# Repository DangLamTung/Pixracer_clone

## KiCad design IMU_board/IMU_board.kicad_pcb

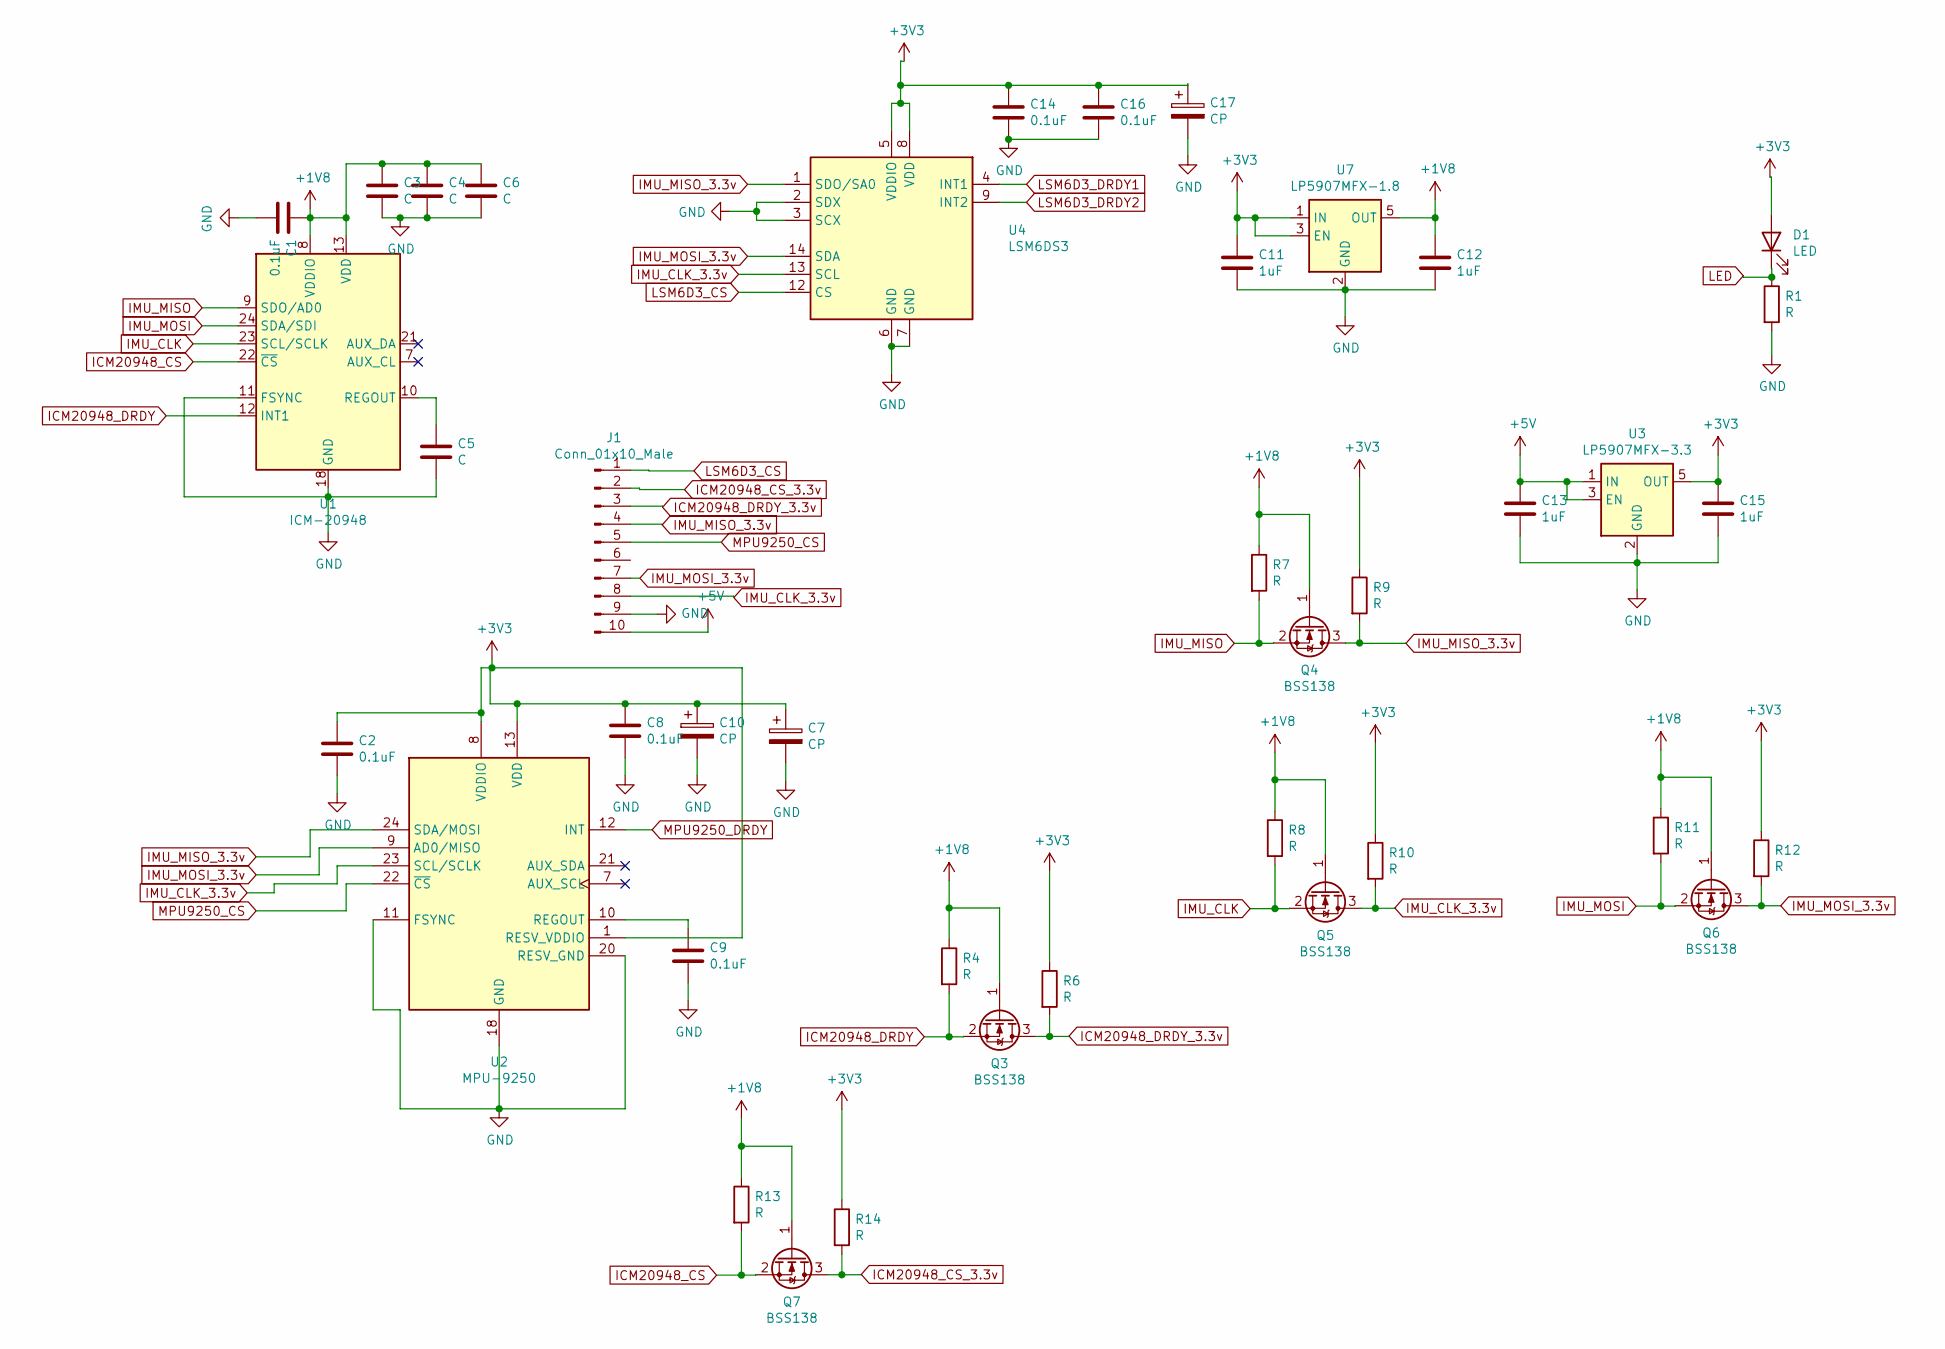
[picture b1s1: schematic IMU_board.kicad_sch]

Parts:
C1, C2, C8, C9, C14, C16: 0.1uF; C_0603_1608Metric
C3, C4, C6: C; C_0603_1608Metric_Pad1.05x0.95mm_HandSolder
C5: C; C_0603_1608Metric
C7, C17: CP; C_1206_3216Metric
C10: CP; C_0603_1608Metric_Pad1.05x0.95mm_HandSolder
C11, C12, C13, C15: 1uF; C_0603_1608Metric_Pad1.05x0.95mm_HandSolder
D1: LED; LED_0603_1608Metric_Pad1.05x0.95mm_HandSolder
J1: Conn_01x10_Male; PinHeader_1x10_P2.54mm_Vertical
Q3, Q4, Q5, Q6, Q7: BSS138; SOT-23
R1, R4, R6, R7, R8, R9, R10, R11, R12, R13, R14: R; R_0603_1608Metric_Pad1.05x0.95mm_HandSolder
U1: ICM-20948; InvenSense_QFN-24_3x3mm_P0.4mm
U2: MPU-9250; InvenSense_QFN-24_3x3mm_P0.4mm
U3: LP5907MFX-3.3; SOT-23-5
U4: LSM6DS3; LGA-14_3x2.5mm_P0.5mm_LayoutBorder3x4y
U7: LP5907MFX-1.8; SOT-23-5

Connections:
+1V8: C1.1, C3.1, C4.1, C6.1, C12.1, Q3.1 (G), Q4.1 (G), Q5.1 (G), Q6.1 (G), Q7.1 (G), R4.1, R7.1, R8.1, R11.1, R13.1, U1.8 (VDDIO), U1.13 (VDD), U7.5 (OUT)
+3V3: C2.1, C7.1, C8.1, C10.1, C11.1, C14.1, C15.1, C16.1, C17.1, D1.2 (A), R6.1, R9.1, R10.1, R12.1, R14.1, U2.1 (RESV_VDDIO), U2.8 (VDDIO), U2.13 (VDD), U3.5 (OUT), U4.5 (VDDIO), U4.8 (VDD), U7.1 (IN), U7.3 (EN)
+5V: C13.1, J1.10, U3.1 (IN), U3.3 (EN)
GND: C1.2, C2.2, C3.2, C4.2, C5.2, C6.2, C7.2, C8.2, C9.2, C10.2, C11.2, C12.2, C13.2, C14.2, C15.2, C16.2, C17.2, J1.9, R1.2, U1.11 (FSYNC), U1.18 (GND), U1.20 (GND), U2.11 (FSYNC), U2.18 (GND), U2.20 (RESV_GND), U3.2 (GND), U4.2 (SDX), U4.3 (SCX), U4.6 (GND), U4.7 (GND), U7.2 (GND)
ICM20948_CS: Q7.2 (S), R13.2, U1.22 (~CS)
ICM20948_CS_3.3v: J1.2, Q7.3 (D), R14.2
ICM20948_DRDY: Q3.2 (S), R4.2, U1.12 (INT1)
ICM20948_DRDY_3.3v: J1.3, Q3.3 (D), R6.2
IMU_CLK: Q5.2 (S), R8.2, U1.23 (SCL/SCLK)
IMU_CLK_3.3v: J1.8, Q5.3 (D), R10.2, U2.23 (SCL/SCLK), U4.13 (SCL)
IMU_MISO: Q4.2 (S), R7.2, U1.9 (SDO/AD0)
IMU_MISO_3.3v: J1.4, Q4.3 (D), R9.2, U2.24 (SDA/MOSI), U4.1 (SDO/SA0)
IMU_MOSI: Q6.2 (S), R11.2, U1.24 (SDA/SDI)
IMU_MOSI_3.3v: J1.7, Q6.3 (D), R12.2, U2.9 (AD0/MISO), U4.14 (SDA)
LED: D1.1 (K), R1.1
LSM6D3_CS: J1.1, U4.12 (CS)
LSM6D3_DRDY1: U4.4 (INT1)
LSM6D3_DRDY2: U4.9 (INT2)
MPU9250_CS: J1.5, U2.22 (~CS)
MPU9250_DRDY: U2.12 (INT)
unnamed: C5.1, U1.10 (REGOUT)
unnamed: C9.1, U2.10 (REGOUT)

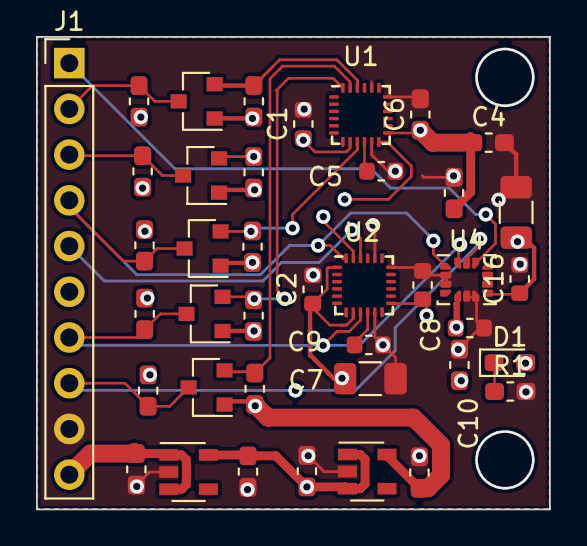
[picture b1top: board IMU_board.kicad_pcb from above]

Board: 4 copper layers, 28.5 x 26.2 mm, 40 parts (0 on the bottom side), 19 nets.

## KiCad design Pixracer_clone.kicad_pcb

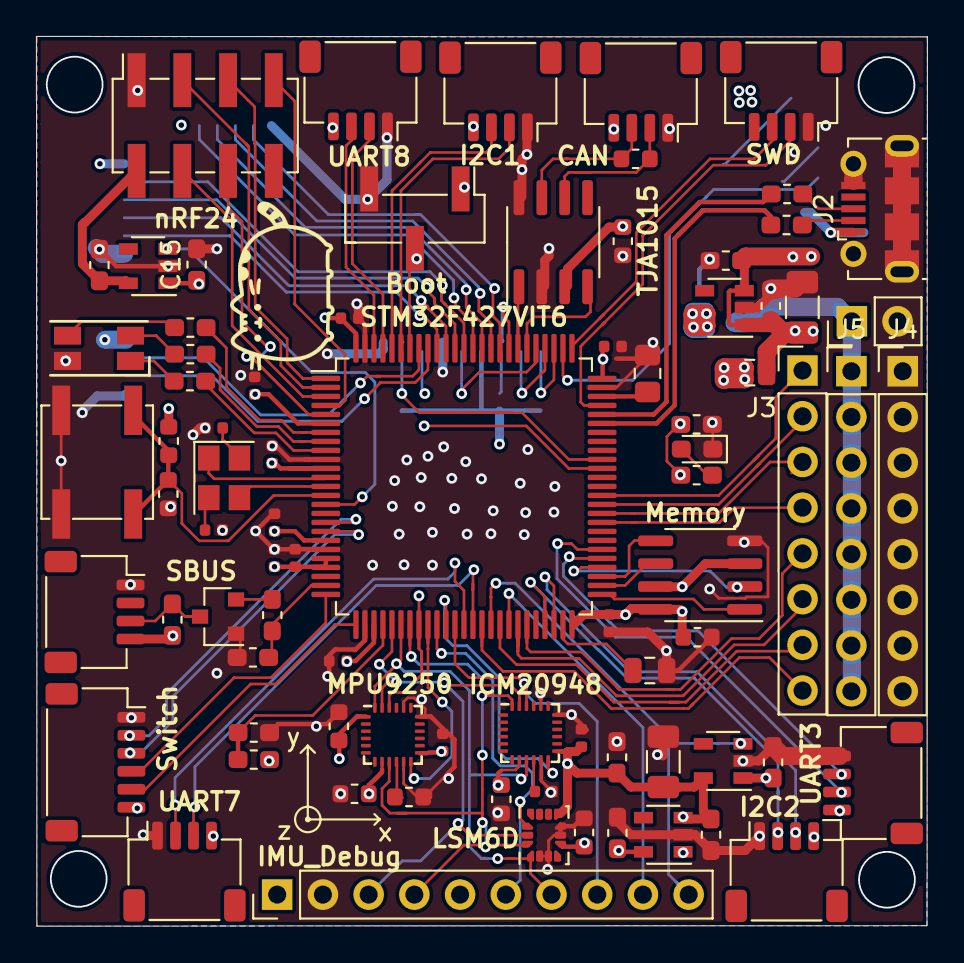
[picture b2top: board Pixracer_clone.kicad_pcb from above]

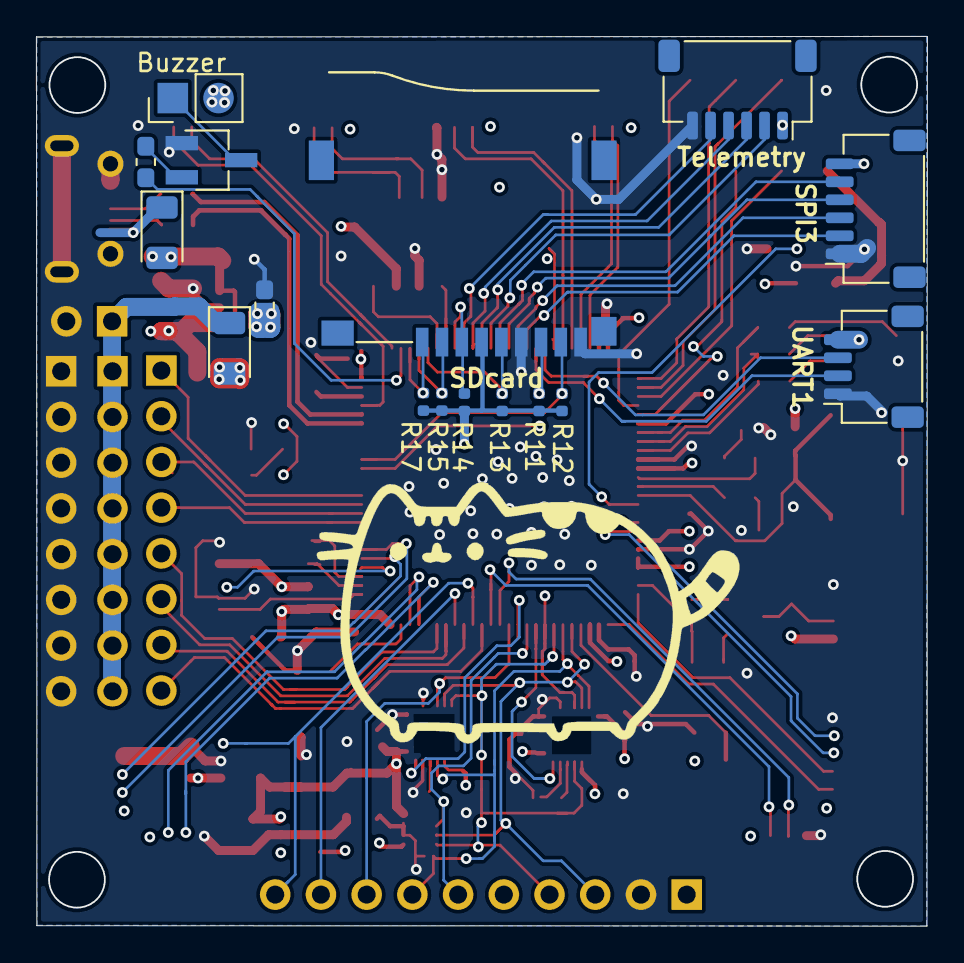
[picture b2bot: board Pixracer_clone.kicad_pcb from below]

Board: 4 copper layers, 49.5 x 49.4 mm, 98 parts (16 on the bottom side), 101 nets.

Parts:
Boot: Conn_01x03_Male; PinHeader_1x03_P2.54mm_Vertical_SMD_Pin1Left
Buzzer: Conn_01x02_Male; PinHeader_1x02_P2.54mm_Vertical
C1: CP; C_0805_2012Metric_Pad1.15x1.40mm_HandSolder
C2, C4: 22p; C_0402_1005Metric
C3: CP; C_0805_2012Metric
C5, C6, C8, C9, C12, C13, C14, C40: 100n; C_0402_1005Metric
C7, C34: 100n; C_0603_1608Metric
C10: 1u; C_0402_1005Metric
C15, C28, C29, C30, C31, C43: 1uF; C_0603_1608Metric_Pad1.05x0.95mm_HandSolder
C16, C23, C24, C26, C42: 0.1uF; C_0603_1608Metric
C17, C19, C20: C; C_0402_1005Metric
C21: C; C_0603_1608Metric
C25, C35: CP; C_1206_3216Metric
C36, C37, C38, C39: 100n; C_0603_1608Metric_Pad1.05x0.95mm_HandSolder
CAN: Conn_01x04_Male; JST_SH_SM04B-SRSS-TB_1x04-1MP_P1.00mm_Horizontal
D1, D2: DIODE; D_1206_3216Metric
D3: LED_RGBA; LED_RGB_1210
D6: LED; LED_0603_1608Metric_Pad1.05x0.95mm_HandSolder
FB1: Ferrite_Bead; R_0805_2012Metric
I2C1, I2C2: UART4_con; JST_SH_SM04B-SRSS-TB_1x04-1MP_P1.00mm_Horizontal
ICM20948: ICM-20948; InvenSense_QFN-24_3x3mm_P0.4mm
IMU_Debug: Conn_01x10_Male; PinHeader_1x10_P2.54mm_Vertical
J2: USB_B_Micro; USB_Micro-B_Molex-105017-0001
J3, J4, J5: Conn_01x08_Male; PinHeader_1x08_P2.54mm_Vertical
J19: Conn_01x02_Male; PinHeader_1x02_P2.54mm_Vertical
LSM6D: LSM6DS3; LGA-14_3x2.5mm_P0.5mm_LayoutBorder3x4y
MPU9250: MPU-9250; InvenSense_QFN-24_3x3mm_P0.4mm
Memory: 25LCxxx; SOIC-8-1EP_3.9x4.9mm_P1.27mm_EP2.29x3mm
Q1: 2N3904; SC-59_Handsoldering
Q2: 2N3904; SOT-23
R1: R; R_0603_1608Metric
R2, R7, R8, R9, R10: R; R_0603_1608Metric_Pad1.05x0.95mm_HandSolder
R3, R4: 22R; R_0603_1608Metric_Pad1.05x0.95mm_HandSolder
R5, R6: 10k; R_0603_1608Metric_Pad1.05x0.95mm_HandSolder
R11, R12, R13, R14, R15, R17: R; R_0402_1005Metric
R16: R; C_0603_1608Metric
Rb_sbus1: 330R; R_0603_1608Metric_Pad1.05x0.95mm_HandSolder
Rc_sbus1: 50k; R_0603_1608Metric_Pad1.05x0.95mm_HandSolder
Rc_sbus2: 1.8k; R_0603_1608Metric_Pad1.05x0.95mm_HandSolder
SBUS: Conn_01x04_Male; JST_SH_SM04B-SRSS-TB_1x04-1MP_P1.00mm_Horizontal
SDcard: Micro_SD_Card; SUNTECH_ST-TF-003A
SPI3: Conn_01x06_Male; JST_SH_SM06B-SRSS-TB_1x06-1MP_P1.00mm_Horizontal
STM32F427VIT6: STM32F427VITx; LQFP-100_14x14mm_P0.5mm
SW1: SW_Push; SW_SPST_EVPBF
SWD: Conn_01x04_Male; JST_SH_SM04B-SRSS-TB_1x04-1MP_P1.00mm_Horizontal
Switch: Conn_01x06_Male; JST_SH_SM06B-SRSS-TB_1x06-1MP_P1.00mm_Horizontal
TJA1015: TJA1051T; SOIC-8_3.9x4.9mm_P1.27mm
Telemetry: Conn_01x06_Male; JST_SH_SM06B-SRSS-TB_1x06-1MP_P1.00mm_Horizontal
U2, U8, U10: LP5907MFX-3.3; SOT-23-5
U7: LP5907MFX-1.8; SOT-23-5
UART1, UART7, UART8: Conn_01x04_Male; JST_SH_SM04B-SRSS-TB_1x04-1MP_P1.00mm_Horizontal
UART3: UART4_con; JST_SH_SM04B-SRSS-TB_1x04-1MP_P1.00mm_Horizontal
Y1: Crystal_GND24; Crystal_SMD_3225-4Pin_3.2x2.5mm
nRF24: NRF24L01_Breakout; PinSocket_2x04_P2.54mm_Vertical_SMD
x: indicator

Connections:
3.3_SENSE_EN: IMU_Debug.10, STM32F427VIT6.41, U8.3
5V_SENSE: R5.2, R6.1, STM32F427VIT6.29
+1V8: C16.1, C29.1, C42.1, ICM20948.8, MPU9250.8, U7.5
+3.3VA: C17.1, C20.1, C23.1, C25.1, C26.1, C28.1, C31.1, ICM20948.13, LSM6D.5, LSM6D.8, MPU9250.1, MPU9250.13, U7.1, U7.3, U8.5
+5V: Buzzer.2, C15.1, C21.1, C30.1, CAN.4, D2.1, I2C1.4, I2C2.4, IMU_Debug.1, J5.1, J5.2, J5.3, J5.4, J5.5, J5.6, J5.7, J5.8, J19.1, R5.1, Rc_sbus2.2, SBUS.4, SPI3.6, Switch.6, TJA1015.3, Telemetry.1, U2.1, U8.1, UART1.4, UART3.1, UART7.4, UART8.4
/CAN_sheet/CAN+: CAN.3, R16.1, TJA1015.7
/CAN_sheet/CAN-: CAN.2, R16.2, TJA1015.6
/USB_sheet/D+: J2.3, R3.1
/USB_sheet/D-: J2.2, R4.1
BATT_CURRENT_SENSE: STM32F427VIT6.26, Switch.5
BATT_VOLT_SENSE: STM32F427VIT6.25, Switch.4
BOOT0: Boot.2, STM32F427VIT6.94
Buzzer: R2.1, STM32F427VIT6.77
CAN1_RX: STM32F427VIT6.81, TJA1015.4
CAN1_TX: STM32F427VIT6.82, TJA1015.1
EXTERNAL_MEM_CS: Memory.1, STM32F427VIT6.51
EXTERNAL_MPU_CS: IMU_Debug.9, STM32F427VIT6.43
GND: Boot.3, C1.2, C2.2, C3.2, C4.2, C5.2, C6.2, C7.2, C8.2, C9.2, C10.2, C12.2, C13.2, C14.2, C15.2, C16.2, C17.2, C19.2, C20.2, C21.2, C23.2, C24.2, C25.2, C26.2, C28.2, C29.2, C30.2, C31.2, C34.2, C35.2, C36.2, C37.2, C38.2, C39.2, C40.2, C42.2, C43.2, CAN.1, D3.4, D6.1, I2C1.1, I2C2.1, ICM20948.11, ICM20948.18, ICM20948.20, IMU_Debug.2, J2.5, J2.6, J4.1, J4.2, J4.3, J4.4, J4.5, J4.6, J4.7, J4.8, J19.2, LSM6D.2, LSM6D.3, LSM6D.6, LSM6D.7, MPU9250.11, MPU9250.18, MPU9250.20, Memory.4, Q1.1, Q2.1, R6.2, Rc_sbus1.1, SBUS.1, SDcard.6, SDcard.9, SPI3.1, STM32F427VIT6.10, STM32F427VIT6.20, STM32F427VIT6.27, STM32F427VIT6.74, STM32F427VIT6.99, SW1.1, SWD.1, Switch.1, TJA1015.2, TJA1015.8, Telemetry.6, U2.2, U7.2, U8.2, U10.2, UART1.1, UART3.4, UART7.1, UART8.1, nRF24.1
I2C2_SCl: I2C2.2, STM32F427VIT6.47
I2C2_SDA: I2C2.3, STM32F427VIT6.48
I2C_SCl: I2C1.2, STM32F427VIT6.95
I2C_SDA: I2C1.3, STM32F427VIT6.96
ICM20948_CS: ICM20948.22, IMU_Debug.8, STM32F427VIT6.37
ICM20948_DRDY: ICM20948.12, STM32F427VIT6.36
IMU_CLK: ICM20948.23, IMU_Debug.3, LSM6D.13, MPU9250.23, STM32F427VIT6.30
IMU_MISO: ICM20948.9, IMU_Debug.7, LSM6D.1, MPU9250.24, STM32F427VIT6.31
IMU_MOSI: ICM20948.24, IMU_Debug.4, LSM6D.14, MPU9250.9, STM32F427VIT6.32
LED1: R7.1, STM32F427VIT6.7
LED2: R8.1, STM32F427VIT6.8
LED3: R9.1, STM32F427VIT6.9
LED_SAFETY: STM32F427VIT6.17, Switch.2
LSM6D3_CS: IMU_Debug.6, LSM6D.12, STM32F427VIT6.35
MPU9250_CS: IMU_Debug.5, MPU9250.22, STM32F427VIT6.33
MPU9250_DRDY: MPU9250.12, STM32F427VIT6.34
NRST: C7.1, R1.2, STM32F427VIT6.14, SW1.2
unnamed: C2.1, Y1.4
unnamed: C4.1, Y1.2
unnamed: C19.1, ICM20948.10
unnamed: C24.1, MPU9250.10
unnamed: C43.1, U2.5, nRF24.2
unnamed: D2.2, FB1.1
unnamed: D3.1, R9.2
unnamed: D3.2, R8.2
unnamed: D3.3, R7.2
unnamed: D6.2, R10.2
unnamed: Buzzer.1, Q1.3
unnamed: Q1.2, R2.2
unnamed: Q2.2, Rb_sbus1.1
OSC1+: STM32F427VIT6.12, Y1.1
OSC1-: STM32F427VIT6.13, Y1.3
PWR_IN: C35.1, C36.1, C37.1, D1.2, FB1.2, U10.1, U10.3
SAFETY_SWITCH_IN: STM32F427VIT6.18, Switch.3
SBUS: Rb_sbus1.2, Rc_sbus1.2, STM32F427VIT6.24
SBUS_DEVICE: Q2.3, Rc_sbus2.1, SBUS.3
SDIO0: R11.2, SDcard.7, STM32F427VIT6.65
SDIO1: R12.2, SDcard.8, STM32F427VIT6.66
SDIO2: R17.2, SDcard.1, STM32F427VIT6.78
SDIO3: R15.2, SDcard.2, STM32F427VIT6.79
SDIO_CLK: R13.2, SDcard.5, STM32F427VIT6.80
SDIO_CMD: R14.2, SDcard.3, STM32F427VIT6.83
SPI2_MISO: Memory.5, STM32F427VIT6.53
SPI2_MOSI: Memory.2, STM32F427VIT6.54
SPI2_SCK: Memory.6, STM32F427VIT6.52
SPI3_CS: SPI3.5, STM32F427VIT6.88
SPI3_MISO: SPI3.3, STM32F427VIT6.90
SPI3_MOSI: SPI3.2, STM32F427VIT6.91
SPI3_SCK: SPI3.4, STM32F427VIT6.89
SPI4_CE: STM32F427VIT6.2, nRF24.3
SPI4_CLK: STM32F427VIT6.1, nRF24.5
SPI4_CS: STM32F427VIT6.3, nRF24.4
SPI4_MISO: STM32F427VIT6.4, nRF24.7
SPI4_MOSI: STM32F427VIT6.5, nRF24.6
SWCLK: STM32F427VIT6.76, SWD.3
SWDIO: STM32F427VIT6.72, SWD.2
TIM1_CH1: J3.8, STM32F427VIT6.40
TIM1_CH2: J3.7, STM32F427VIT6.42
TIM1_CH3: J3.6, STM32F427VIT6.44
TIM1_CH4: J3.5, STM32F427VIT6.45
TIM3_CH1: J3.4, STM32F427VIT6.59
TIM3_CH2: J3.3, STM32F427VIT6.60
TIM3_CH3: J3.2, STM32F427VIT6.61
TIM3_CH4: J3.1, STM32F427VIT6.62
UART1_RX: STM32F427VIT6.93, UART1.3
UART1_TX: STM32F427VIT6.92, UART1.2
UART2_CTS: STM32F427VIT6.84, Telemetry.5
UART2_RTS: STM32F427VIT6.85, Telemetry.4
UART2_RX: STM32F427VIT6.87, Telemetry.2
UART2_TX: STM32F427VIT6.86, Telemetry.3
UART3_RX: STM32F427VIT6.55, UART3.3
UART3_TX: STM32F427VIT6.56, UART3.2
UART7_RX: STM32F427VIT6.38, UART7.2
UART7_TX: STM32F427VIT6.39, UART7.3
UART8_RX: STM32F427VIT6.97, UART8.2
UART8_TX: STM32F427VIT6.98, UART8.3
USB_D+: R3.2, STM32F427VIT6.71
USB_D-: R4.2, STM32F427VIT6.70
VBUS: D1.1, J2.1
VCAP_1: C3.1, STM32F427VIT6.49
VCAP_2: C1.1, STM32F427VIT6.73
VCC: Boot.1, C5.1, C6.1, C8.1, C9.1, C10.1, C12.1, C13.1, C14.1, C34.1, C38.1, C39.1, C40.1, Memory.3, Memory.7, Memory.8, R1.1, R10.1, R11.1, R12.1, R13.1, R14.1, R15.1, R17.1, SDcard.4, STM32F427VIT6.6, STM32F427VIT6.11, STM32F427VIT6.19, STM32F427VIT6.21, STM32F427VIT6.22, STM32F427VIT6.28, STM32F427VIT6.50, STM32F427VIT6.75, STM32F427VIT6.100, U10.5
nRF24_EN: STM32F427VIT6.15, U2.3

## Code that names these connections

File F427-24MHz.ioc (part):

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Mcu.Name=STM32F427V(G-I)Tx
Mcu.Package=LQFP100
Mcu.UserName=STM32F427VITx
PA0/WKUP.Mode=Asynchronous
PA0/WKUP.Signal=UART4_TX
PA1.Mode=Asynchronous
PA1.Signal=UART4_RX
PA10.Mode=Asynchronous
PA10.Signal=USART1_RX
PA11.Mode=Device_Only
PA11.Signal=USB_OTG_FS_DM
PA12.Mode=Device_Only
PA12.Signal=USB_OTG_FS_DP
PA13.Mode=Serial_Wire
PA13.Signal=SYS_JTMS-SWDIO
PA14.Mode=Serial_Wire
PA14.Signal=SYS_JTCK-SWCLK
PA2.Signal=ADCx_IN2
PA3.Signal=ADCx_IN3
PA4.Signal=ADCx_IN4
PA5.Mode=Full_Duplex_Master
PA5.Signal=SPI1_SCK
PA6.Mode=Full_Duplex_Master
PA6.Signal=SPI1_MISO
PA7.Mode=Full_Duplex_Master
PA7.Signal=SPI1_MOSI
PA8.Mode=Clock-out-1
PA8.Signal=RCC_MCO_1
PA9.Mode=Asynchronous
PA9.Signal=USART1_TX
PB0.Signal=GPIO_Output
PB1.Signal=GPIO_Output
PB10.Mode=I2C
PB10.Signal=I2C2_SCL
PB11.Mode=I2C
PB11.Signal=I2C2_SDA
PB12.Signal=GPIO_Output
PB13.Mode=Full_Duplex_Master
PB13.Signal=SPI2_SCK
PB14.Mode=Full_Duplex_Master
PB14.Signal=SPI2_MISO
PB15.Mode=Full_Duplex_Master
PB15.Signal=SPI2_MOSI
PB2/BOOT1.Signal=GPIO_Output
PB3.Mode=Full_Duplex_Master
PB3.Signal=SPI3_SCK
PB4.Mode=Full_Duplex_Master
PB4.Signal=SPI3_MISO
PB5.Mode=Full_Duplex_Master
PB5.Signal=SPI3_MOSI
PB6.Mode=I2C
PB6.Signal=I2C1_SCL
PB7.Mode=I2C
PB7.Signal=I2C1_SDA
PC10.Mode=SD_4_bits_Wide_bus
PC10.Signal=SDIO_D2
PC11.Mode=SD_4_bits_Wide_bus
PC11.Signal=SDIO_D3
PC12.Mode=SD_4_bits_Wide_bus
PC12.Signal=SDIO_CK
PC4.Signal=GPIO_Output
PC5.Signal=GPIO_Output
PC6.Mode=Asynchronous
PC6.Signal=USART6_TX
PC7.Mode=Asynchronous
PC7.Signal=USART6_RX
PC8.Mode=SD_4_bits_Wide_bus
PC8.Signal=SDIO_D0
PC9.Mode=SD_4_bits_Wide_bus
PC9.Signal=SDIO_D1
PD0.Mode=Master
PD0.Signal=CAN1_RX
PD1.Mode=Master
PD1.Signal=CAN1_TX
PD12.Signal=S_TIM4_CH1
PD13.Signal=S_TIM4_CH2
PD14.Signal=S_TIM4_CH3
PD15.Signal=S_TIM4_CH4
PD2.Mode=SD_4_bits_Wide_bus
PD2.Signal=SDIO_CMD
PD3.Mode=CTS_RTS
PD3.Signal=USART2_CTS
PD4.Mode=CTS_RTS
PD4.Signal=USART2_RTS
PD5.Mode=Asynchronous
PD5.Signal=USART2_TX
PD6.Mode=Asynchronous
PD6.Signal=USART2_RX
PD8.Mode=Asynchronous
PD8.Signal=USART3_TX
PD9.Mode=Asynchronous
PD9.Signal=USART3_RX
PE0.Mode=Asynchronous
PE0.Signal=UART8_RX
PE1.Mode=Asynchronous
PE1.Signal=UART8_TX
PE11.Signal=S_TIM1_CH2
PE13.Signal=S_TIM1_CH3
PE14.Signal=S_TIM1_CH4
PE2.Mode=Full_Duplex_Master
PE2.Signal=SPI4_SCK
PE5.Mode=Full_Duplex_Master
PE5.Signal=SPI4_MISO
PE6.Mode=Full_Duplex_Master
PE6.Signal=SPI4_MOSI
PE7.Mode=Asynchronous
PE7.Signal=UART7_RX
PE8.Mode=Asynchronous
PE8.Signal=UART7_TX
PE9.Signal=S_TIM1_CH1
PH0/OSC_IN.Mode=HSE-External-Oscillator
PH0/OSC_IN.Signal=RCC_OSC_IN
PH1/OSC_OUT.Mode=HSE-External-Oscillator
PH1/OSC_OUT.Signal=RCC_OSC_OUT
RCC.HSE_VALUE=24000000
RCC.SYSCLKFreq_VALUE=168000000
RCC.SYSCLKSource=RCC_SYSCLKSOURCE_PLLCLK
board=custom

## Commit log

2020-09-02 finish schematic
2020-09-03 4 layer add
2020-09-03 add alittle
2020-09-04 add alot
2020-09-07 finish board
2020-09-20 add IMU external board
2020-09-21 Create fp-info-cache
2020-09-21 add led
